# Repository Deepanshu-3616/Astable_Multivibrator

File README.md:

## Visuals

<table style="width:100%">
  <tr>
    <th style="text-align:center">3D Render</th>
    <th style="text-align:center">PCB Routing</th>
  </tr>
  <tr>
    <td style="width:50%"></td>
    <td style="width:50%"></td>
  </tr>
</table>

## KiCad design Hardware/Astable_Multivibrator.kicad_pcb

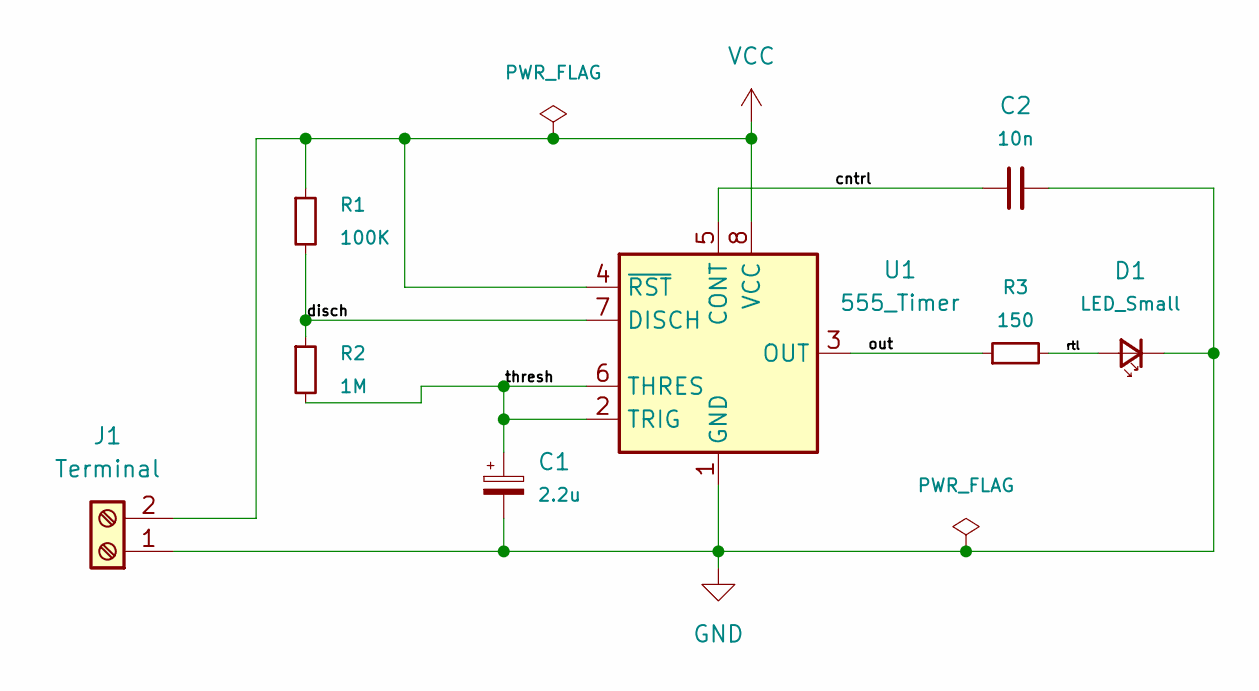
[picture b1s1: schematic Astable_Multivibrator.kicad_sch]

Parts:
C1: 2.2u; CP_Radial_D4.0mm_P1.50mm
C2: 10n; C_Disc_D3.0mm_W1.6mm_P2.50mm
D1: LED_Small; LED_D3.0mm
J1: Terminal; Altech_AK300_1x02_P5.00mm_45-Degree
R1: 100K; R_Axial_DIN0204_L3.6mm_D1.6mm_P1.90mm_Vertical
R2: 1M; R_Axial_DIN0204_L3.6mm_D1.6mm_P1.90mm_Vertical
R3: 150; R_Axial_DIN0204_L3.6mm_D1.6mm_P1.90mm_Vertical
U1: 555_Timer; DIP-8_W7.62mm

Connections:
/cntrl: C2.1, U1.5 (CONT)
/disch: R1.2, R2.1, U1.7 (DISCH)
/out: R3.1, U1.3 (OUT)
/rtl: D1.2 (A), R3.2
/thresh: C1.1, R2.2, U1.2 (TRIG), U1.6 (THRES)
GND: C1.2, C2.2, D1.1 (K), J1.1, U1.1 (GND)
VCC: J1.2, R1.1, U1.4 (~RST), U1.8 (VCC)

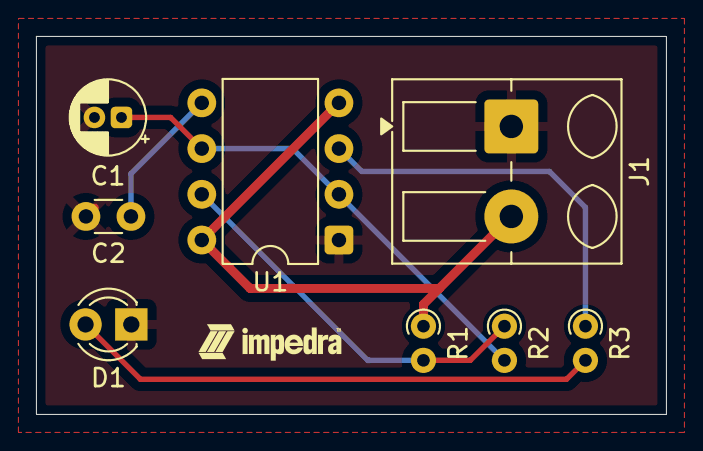
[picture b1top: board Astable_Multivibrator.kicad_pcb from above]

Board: 2 copper layers, 35.0 x 21.0 mm, 8 parts (0 on the bottom side), 7 nets.

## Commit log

2026-06-10 Initial commit: Add hardware source files and Git filter
2026-06-10 Add professional project README
2026-06-10 3D_render & routing visuals into README
2026-06-10 Project Visuals
